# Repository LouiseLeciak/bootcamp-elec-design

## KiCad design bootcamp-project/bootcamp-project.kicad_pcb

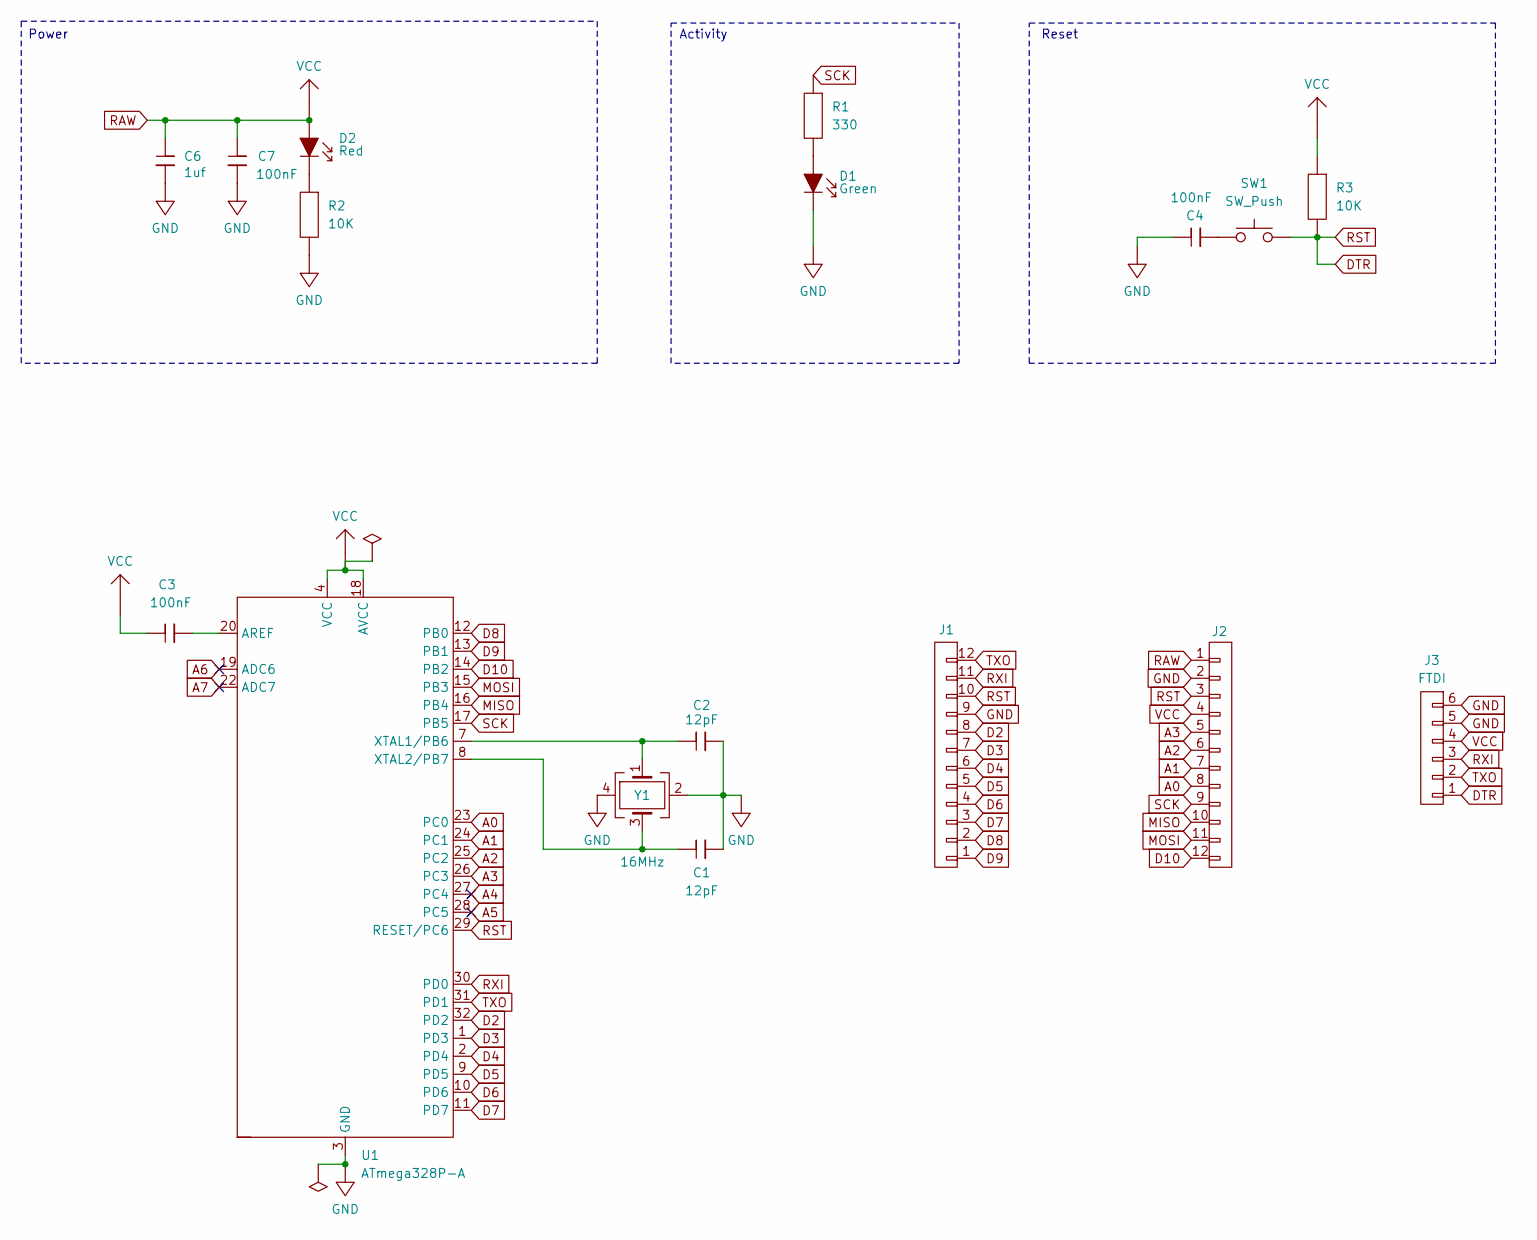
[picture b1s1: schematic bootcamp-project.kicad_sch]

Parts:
C1, C2: 12pF; marge_capacitor
C3, C4, C7: 100nF; marge_capacitor
C6: 1uf; marge_capacitor
D1: Green; marge_led
D2: Red; marge_led
J1: JUMPER_12_J1
J2: JUMPER_12_J2
J3: FTDI; JUMPER_FDTI
R1: 330; marge_resistor
R2, R3: 10K; marge_resistor
SW1: SW_Push; SWITCH_SW
U1: ATmega328P-A; ATMEGA328p
Y1: 16MHz; QUARTZ_16MHz

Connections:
A0: J2.8, U1.23 (PC0)
A1: J2.7, U1.24 (PC1)
A2: J2.6, U1.25 (PC2)
A3: J2.5, U1.26 (PC3)
A4: U1.27 (PC4)
A5: U1.28 (PC5)
A6: U1.19 (ADC6)
A7: U1.22 (ADC7)
D2: J1.8, U1.32 (PD2)
D3: J1.7, U1.1 (PD3)
D4: J1.6, U1.2 (PD4)
D5: J1.5, U1.9 (PD5)
D6: J1.4, U1.10 (PD6)
D7: J1.3, U1.11 (PD7)
D8: J1.2, U1.12 (PB0)
D9: J1.1, U1.13 (PB1)
D10: J2.12, U1.14 (PB2)
DTR: J1.10, J2.3, J3.1, R3.1, SW1.1, U1.29 (RESET/PC6)
MISO: J2.10, U1.16 (PB4)
MOSI: J2.11, U1.15 (PB3)
unnamed: C4.1, SW1.0
unnamed: D1.0, R1.1
unnamed: D2.1, R2.0
unnamed: C3.1, U1.20 (AREF)
unnamed: C2.0, U1.7 (XTAL1/PB6), Y1.1
unnamed: C1.0, U1.8 (XTAL2/PB7), Y1.3
RXI: J1.11, J3.3, U1.30 (PD0)
SCK: J2.9, R1.0, U1.17 (PB5)
TXO: J1.12, J3.2, U1.31 (PD1)

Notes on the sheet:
Power
Activity
Reset

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
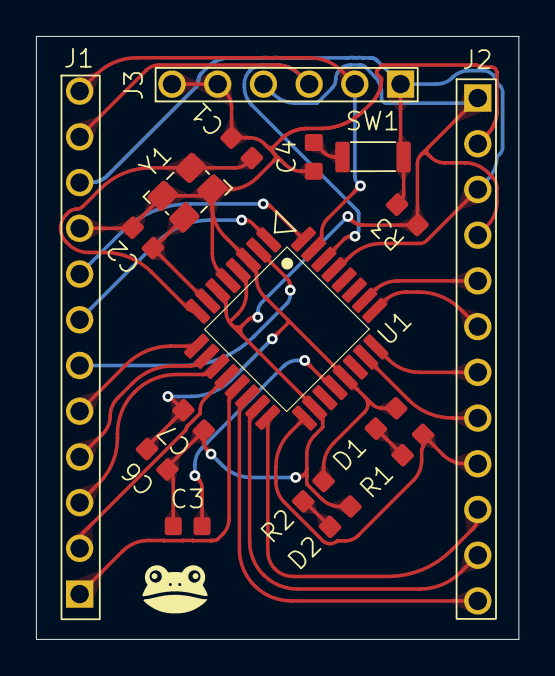
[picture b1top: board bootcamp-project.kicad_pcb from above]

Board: 2 copper layers, 26.8 x 33.5 mm, 17 parts (0 on the bottom side), 27 nets.

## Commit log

2026-05-11 lib: add capacitor and diode symbols
2026-05-11 lib: added capacitor, diode, gnd, light emitting diode, resistor, switch, vcc
2026-05-11 lib: add quartz
2026-05-11 lib: add atmega
2026-05-11 lib: add jumper1/2/3
2026-05-11 lib: typo jumper1/2/3
2026-05-11 lib: typo POWER SYMBOL
2026-05-11 lib: hide some pin nb
2026-05-11 proj: starting atmega
2026-05-11 lib: no more value
2026-05-11 lib: del F in capacitor
2026-05-11 lib: passiv mod
2026-05-11 lib: typo
2026-05-11 schematic: input/output not driven
2026-05-11 all: need fix
2026-05-12 lib: pin change
2026-05-12 all: general fix, no more EDR errors
2026-05-12 foot: starting footprint lib
2026-05-12 foot: funny we had the information late had to restart aahahahahahahhahahahhahaha
2026-05-13 footprints: clean capacitor and resistance, add switch
2026-05-13 footprints: add qwartz
2026-05-13 footprints: add leds
2026-05-13 footprints: add atmega
2026-05-14 lib: fix power flag, foot: add jumpers
2026-05-15 lib: fix schematic with power flags
2026-05-15 foot: add some marge for resistor, capacitor and leds, following the 0603 convention
2026-05-15 foot: clean silkscreen
2026-05-15 lib: connect symbols and footprints
2026-05-15 sche: update schematic'
2026-05-15 foot: change switch
2026-05-15 pcb: start but not that good
2026-05-15 pcb: not viable
2026-05-15 pcb: new try, again
2026-05-17 pcb: everything seems connected
2026-05-17 pcb: all connected, no error, no warning
2026-05-17 foot: design update
2026-05-18 pcb: add ground plane
2026-05-18 foot: fix pad numb
2026-05-18 pcb: remake a clean pcb
2026-05-18 pcb: pcb done
2026-05-20 add: bonuses
